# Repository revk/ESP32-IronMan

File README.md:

# ESP32-IronMan

Now at [Codeberg](https://codeberg.org/RevK/ESP32-IronMan)

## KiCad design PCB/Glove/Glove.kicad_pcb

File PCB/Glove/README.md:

# Glove

These files are for use in [KiCad](https://www.kicad.org).

## Trademark

This is an open source project, but bear in mind you cannot sell boards bearing the Andrews & Arnold Ltd name, the A&A logo, the registered trademark AJK logo, or the GS1 allocated EANs assigned to Andrews & Arnold Ltd.

## Images

*Auto generated 2025-01-28T13:22:18*

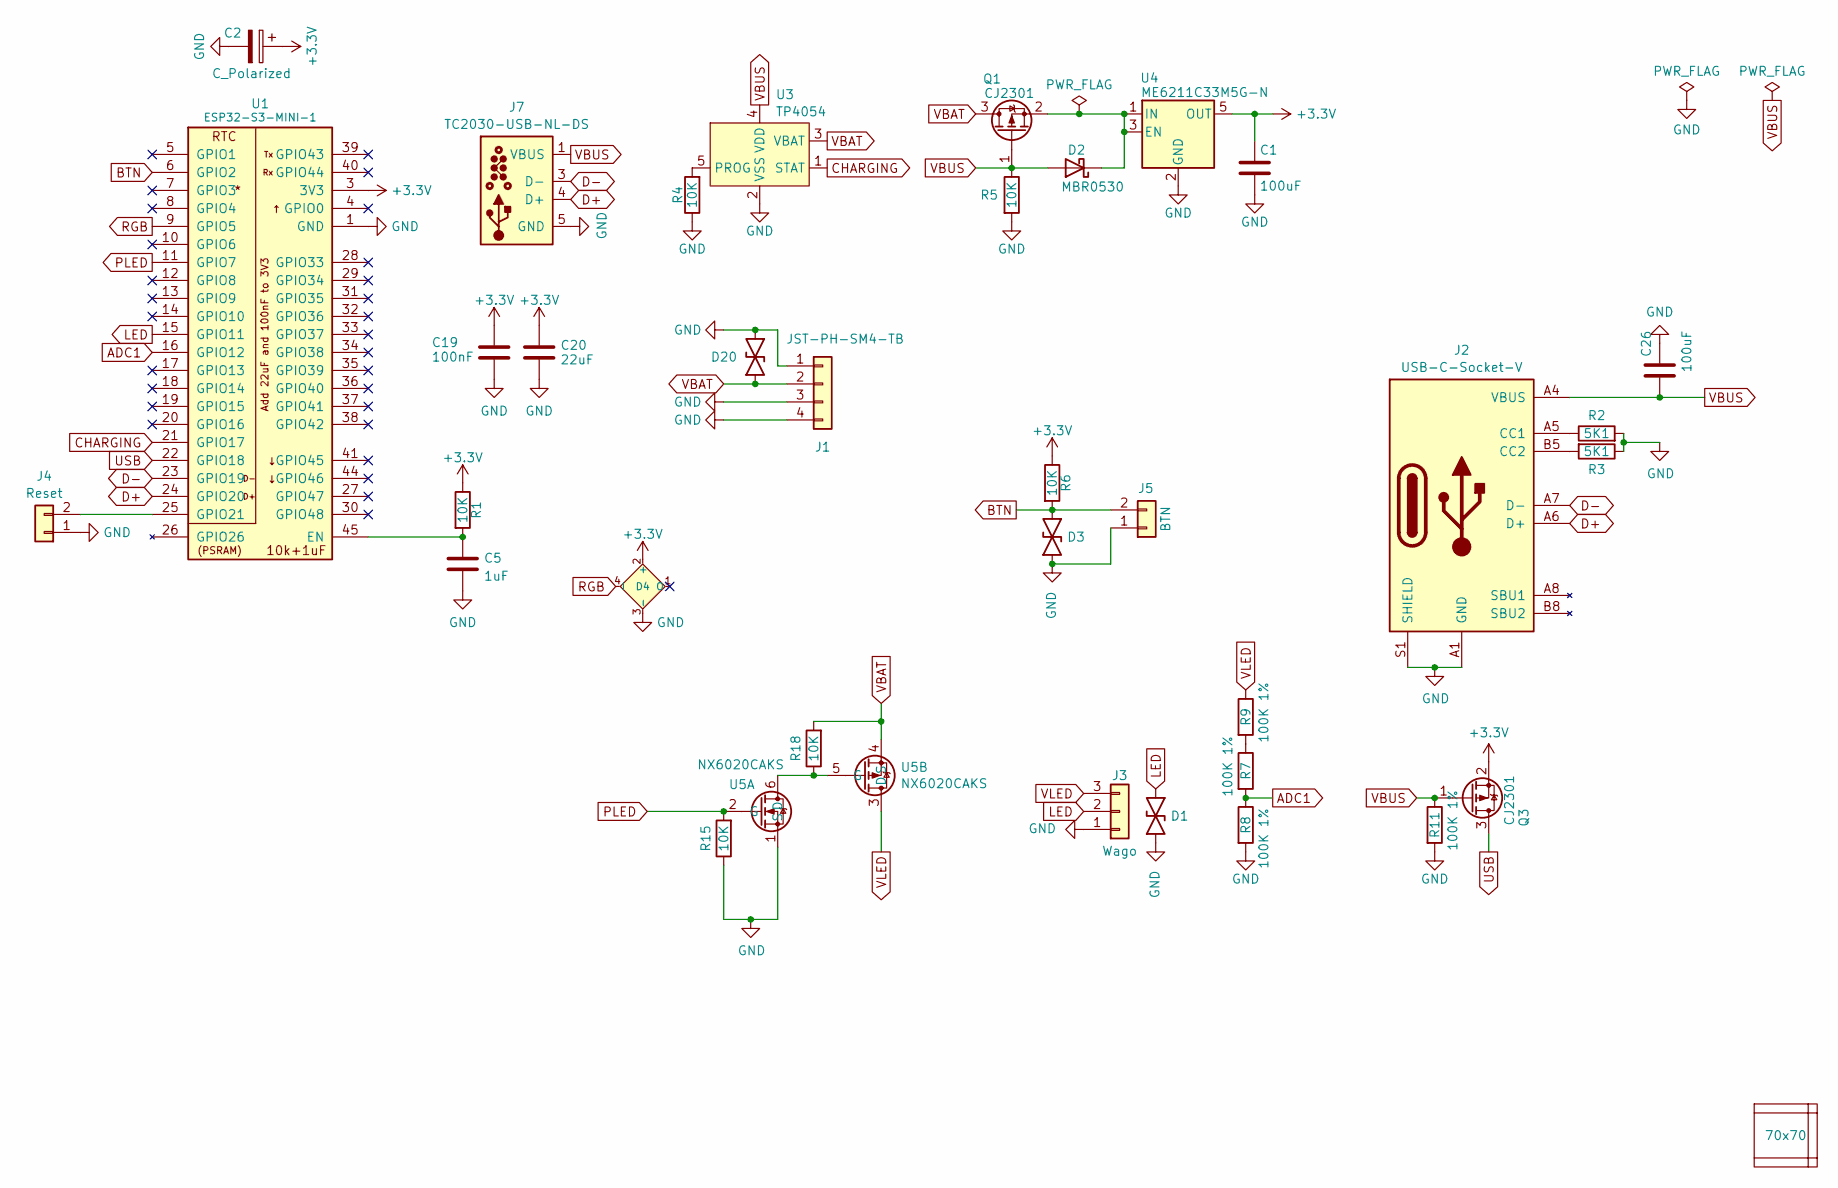
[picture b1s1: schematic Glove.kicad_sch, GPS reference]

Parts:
C1, C26: 100uF; C_0805; MPN C141660
C2: C_Polarized; CP_EIA-7343-31_Kemet-D; MPN C106188
C5: 1uF; C_0402
C19: 100nF; C_0402
C20: 22uF; C_0603
D1, D3, D20: DFN1006-2L; MPN C5137770
D2: MBR0530; D_SOD-123; MPN C5204746
D4: XL-1010RGBC-WS2812B; SMD1010; MPN C5349953
J1: JST-PH-SM4-TB; JST_PH_S2B-PH-SM4-TB_1x02-1MP_P2.00mm_Horizontal; MPN C295747
J2: USB-C-Socket-V; USB-C-Socket-H; MPN C709357
J3: Wago; WAGO-2060-453-998-404; MPN C2765056
J4: Reset; AA-Pad
J5: BTN; WAGO-2060-452-998-404; MPN C2765055
J7: TC2030-USB-NL-DS; Tag-Connect_TC2030-IDC-NL_2x03_P1.27mm_Vertical
PCB1: 70x70; PCB7070
Q1, Q3: CJ2301; SOT-23; MPN C5224170
R1, R4, R5, R6, R15, R18: 10K; R_0402
R2, R3: 5K1; R_0402
R7, R8, R9, R11: 100K 1%; R_0402; MPN C5139597
U1: ESP32-S3-MINI-1; MPN C3013941
U3: TP4054; SOT-23-5; MPN C668215
U4: ME6211C33M5G-N; SOT-23-5; MPN C82942
U5: NX6020CAKS; SOT-363_SC-70-6
V1, V2, V4: VCUT70N

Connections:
+3.3V: C1.1, C2.1, C19.1, C20.1, D4.2 (+), Q3.2 (S), R1.1, R6.1, U1.3 (3V3), U4.5 (OUT)
ADC1: R7.2, R8.1, U1.16 (GPIO12)
BTN: D3.2, J5.2, R6.2, U1.6 (GPIO2)
CHARGING: U1.21 (GPIO17), U3.1 (STAT)
D+: J2.A6 (D+), J2.B6 (D+), J7.4 (D+), U1.24 (GPIO20)
D-: J2.A7 (D-), J2.B7 (D-), J7.2 (NC), J7.3 (D-), J7.6 (NC), U1.23 (GPIO19)
GND: C1.2, C2.2, C5.2, C19.2, C20.2, C26.2, D1.1, D3.1, D4.3 (-), D20.1, J1.1, J1.3, J1.4, J2.A1 (GND), J2.A12 (GND), J2.B1 (GND), J2.B12 (GND), J2.S1 (SHIELD), J3.1, J4.1, J5.1, J7.5 (GND), R2.2, R3.1, R4.1, R5.2, R8.2, R11.2, R15.1, U1.1 (GND), U1.2 (GND), U1.42 (GND), U1.43 (GND), U1.46 (GND), U1.47 (GND), U1.48 (GND), U1.49 (GND), U1.50 (GND), U1.51 (GND), U1.52 (GND), U1.53 (GND), U1.54 (GND), U1.55 (GND), U1.56 (GND), U1.57 (GND), U1.58 (GND), U1.59 (GND), U1.60 (GND), U1.61 (GND), U1.62 (GND), U1.63 (GND), U1.64 (GND), U1.65 (GND), U3.2 (VSS), U4.2 (GND), U5.1 (S)
LED: D1.2, J3.2, U1.15 (GPIO11)
unnamed: D2.1 (K), Q1.2 (S), U4.1 (IN), U4.3 (EN)
unnamed: J2.A5 (CC1), R2.1
unnamed: J2.B5 (CC2), R3.2
unnamed: J4.2, U1.25 (GPIO21)
unnamed: R7.1, R9.2
unnamed: C5.1, R1.2, U1.45 (EN)
unnamed: R4.2, U3.5 (PROG)
unnamed: R18.1, U5.5 (G), U5.6 (D)
PLED: R15.2, U1.11 (GPIO7), U5.2 (G)
RGB: D4.4 (I), U1.9 (GPIO5)
USB: Q3.3 (D), U1.22 (GPIO18)
VBAT: D20.2, J1.2, Q1.3 (D), R18.2, U3.3 (VBAT), U5.4 (S)
VBUS: C26.1, D2.2 (A), J2.A4 (VBUS), J2.A9 (VBUS), J2.B4 (VBUS), J2.B9 (VBUS), J7.1 (VBUS), Q1.1 (G), Q3.1 (G), R5.1, R11.1, U3.4 (VDD)
VLED: J3.3, R9.1, U5.3 (D)

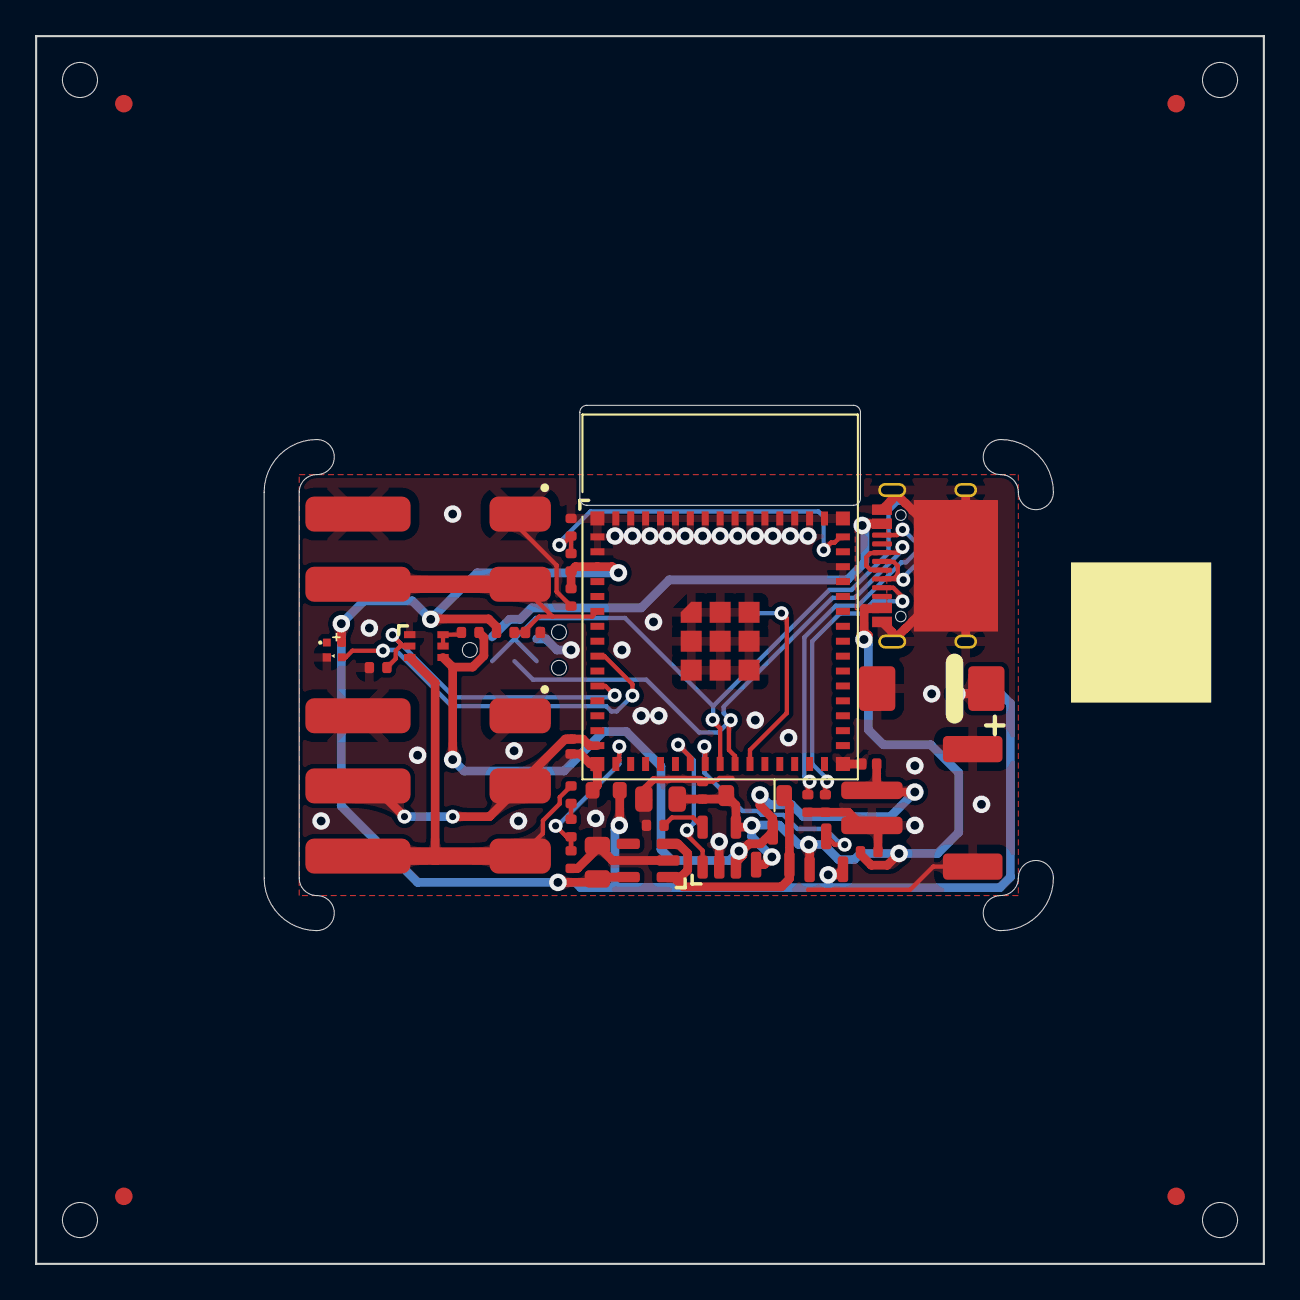
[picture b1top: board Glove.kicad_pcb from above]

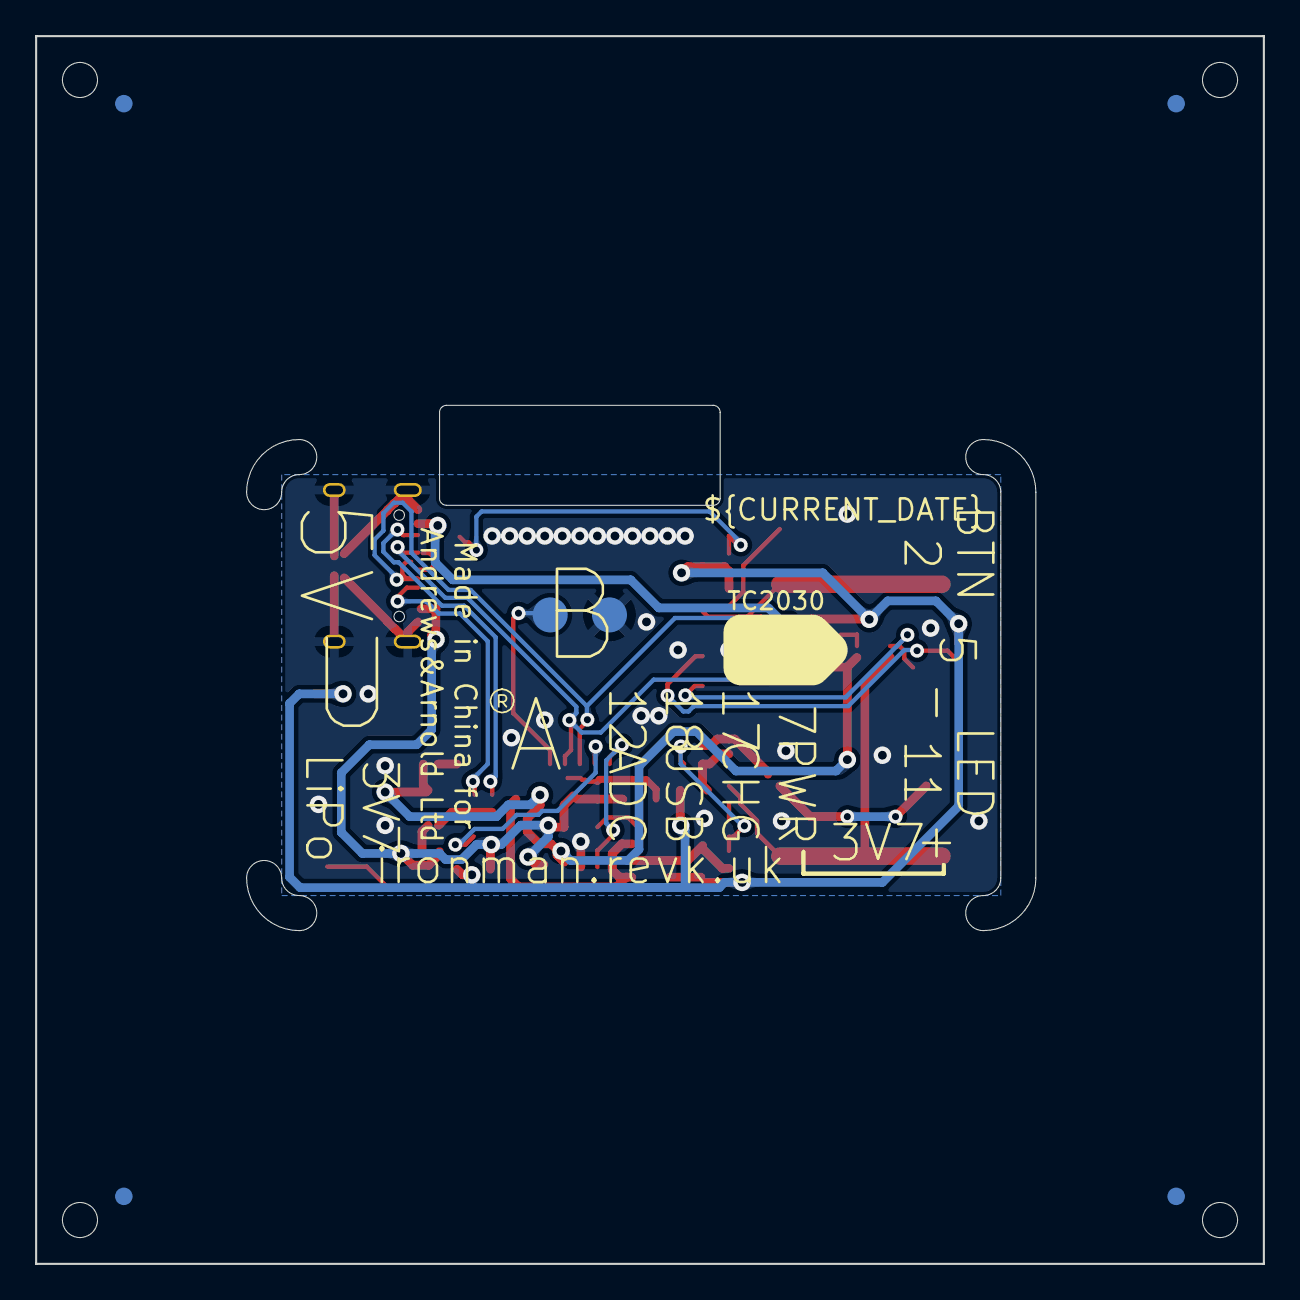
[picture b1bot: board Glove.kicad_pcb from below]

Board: 2 copper layers, 70.0 x 70.0 mm, 39 parts (3 on the bottom side), 22 nets.

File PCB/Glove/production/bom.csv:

Designator,Footprint,Quantity,Value,LCSC Part #
"C1, C26",C_0805,2,100uF,C141660
C19,C_0402,1,100nF,
C2,CP_EIA-7343-31_Kemet-D,1,C_Polarized,C106188
C20,C_0603,1,22uF,
C5,C_0402,1,1uF,
"D1, D20, D3",DFN1006-2L,3,~,C5137770
D2,D_SOD-123,1,MBR0530,C5204746
D4,SMD1010,1,XL-1010RGBC-WS2812B,C5349953
J1,JST_PH_S2B-PH-SM4-TB_1x02-1MP_P2.00mm_Horizontal,1,JST-PH-SM4-TB,C295747
J2,USB-C-Socket-H,1,USB-C-Socket-V,C709357
J3,WAGO-2060-453-998-404,1,Wago,C2765056
J4,AA-Pad,1,Reset,
J5,WAGO-2060-452-998-404,1,BTN,C2765055
"Q1, Q3",SOT-23,2,CJ2301,C5224170
"R1, R15, R18, R4, R5, R6",R_0402,6,10K,
"R11, R7, R8, R9",R_0402,4,100K 1%,C5139597
"R2, R3",R_0402,2,5K1,
U1,ESP32-S3-MINI-1,1,ESP32-S3-MINI-1,C3013941
U3,SOT-23-5,1,TP4054,C668215
U4,SOT-23-5,1,ME6211C33M5G-N,C82942
U5,SOT-363_SC-70-6,1,NX6020CAKS,

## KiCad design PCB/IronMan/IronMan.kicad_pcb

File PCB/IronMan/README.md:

# IronMan

These files are for use in [KiCad](https://www.kicad.org).

## Trademark

This is an open source project, but bear in mind you cannot sell boards bearing the Andrews & Arnold Ltd name, the A&A logo, the registered trademark AJK logo, or the GS1 allocated EANs assigned to Andrews & Arnold Ltd.

## Images

*Auto generated 2025-01-30T09:48:34*

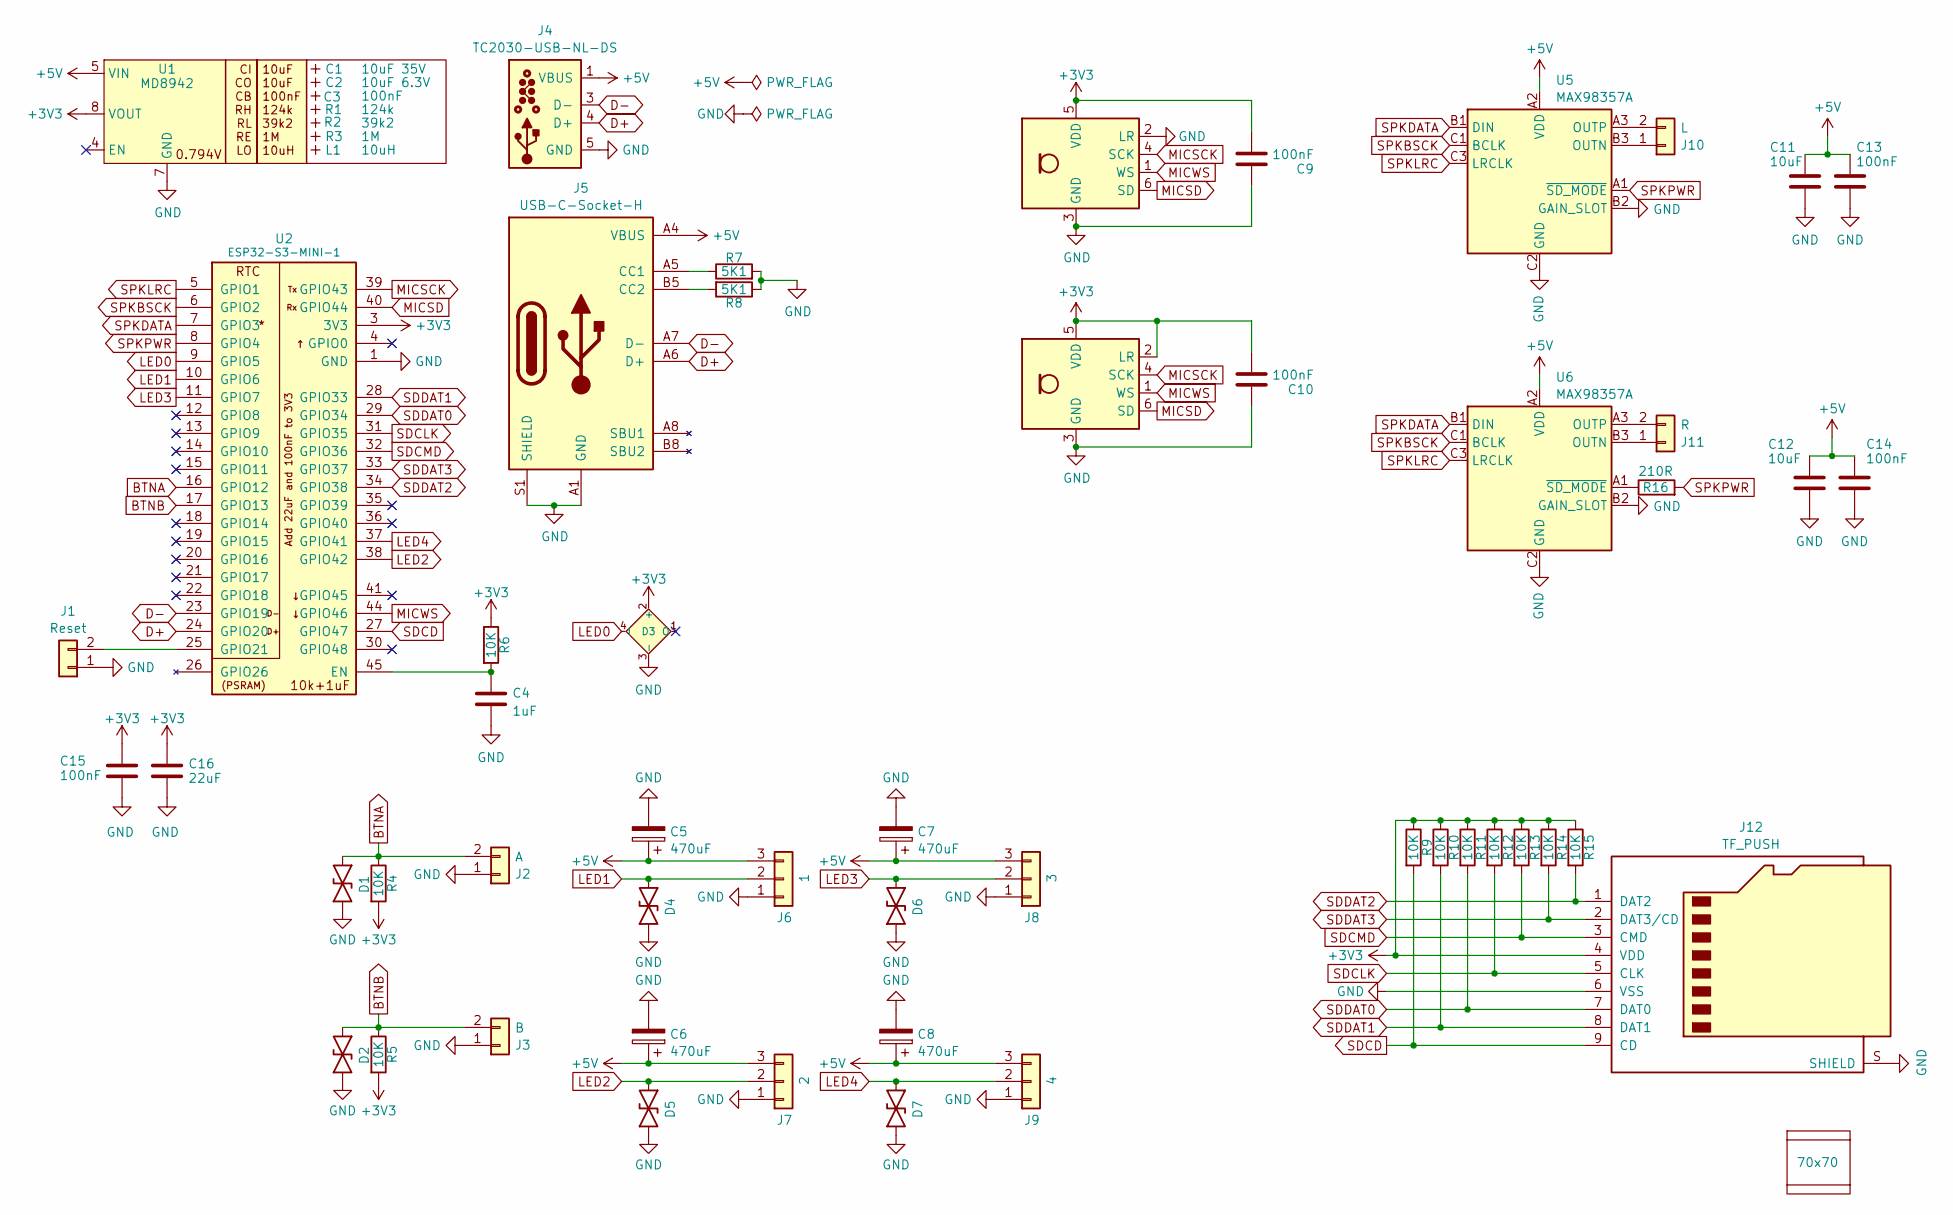
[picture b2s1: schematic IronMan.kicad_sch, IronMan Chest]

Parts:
C1: 10uF 35V; C_0603_; MPN C194427
C2: 10uF 6.3V; C_0603_; MPN C1691
C3: 100nF; C_0603_
C4: 1uF; C_0402
C5, C6, C7, C8: 470uF; CP_EIA-7343-31_Kemet-D; MPN C106188
C9, C10, C13, C14, C15: 100nF; C_0402
C11, C12: 10uF; C_0402; MPN C15525
C16: 22uF; C_0603
D1, D2, D4, D5, D6, D7: DFN1006-2L; MPN C5137770
D3: XL-1010RGBC-WS2812B; SMD1010; MPN C5349953
J1: Reset; AA-Pad
J2: A; WAGO-2060-452-998-404; MPN C2765055
J3: B; WAGO-2060-452-998-404; MPN C2765055
J4: TC2030-USB-NL-DS; Tag-Connect_TC2030-IDC-NL_2x03_P1.27mm_Vertical
J5: USB-C-Socket-H; MPN C709357
J6: 1; WAGO-2060-453-998-404; MPN C2765056
J7: 2; WAGO-2060-453-998-404; MPN C2765056
J8: 3; WAGO-2060-453-998-404; MPN C2765056
J9: 4; WAGO-2060-453-998-404; MPN C2765056
J10: L; WAGO-2060-452-998-404; MPN C2765055
J11: R; WAGO-2060-452-998-404; MPN C2765055
J12: TF_PUSH; MPN C393941
L1: 10uH; L_4x4_
PCB1: 70x70; PCB7070
R1: 124k; R_0402_
R2: 39k2; R_0402_
R3: 1M; R_0402_
R4, R5, R6, R9, R10, R11, R12, R13, R14, R15: 10K; R_0402
R7, R8: 5K1; R_0402
R16: 210R; R_0402; MPN C226891
U1: MD8942; SOT-23-6-MD8942; MPN C2684786
U2: ESP32-S3-MINI-1; MPN C3013941
U3: L; ICS43434_MEMS_Mic; MPN C5656610
U4: R; ICS43434_MEMS_Mic; MPN C5656610
U5, U6: MAX98357A; WLP-1.437mmx1.347mm-0.21mm-ball; MPN C2682619
V2, V3: VCUT70N

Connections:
+3V3: C9.2, C10.2, C15.1, C16.1, D3.2 (+), J12.4 (VDD), R4.2, R5.2, R6.1, R9.1, R10.1, R11.1, R12.1, R13.1, R14.1, R15.1, U1.8 (VOUT), U2.3 (3V3), U3.5 (VDD), U4.2 (LR), U4.5 (VDD)
+5V: C5.1, C6.1, C7.1, C8.1, C11.1, C12.1, C13.1, C14.1, J4.1 (VBUS), J5.A4 (VBUS), J5.A9 (VBUS), J5.B4 (VBUS), J5.B9 (VBUS), J6.3, J7.3, J8.3, J9.3, U1.5 (VIN), U5.A2 (VDD), U6.A2 (VDD)
BTNA: D1.1, J2.2, R4.1, U2.16 (GPIO12)
BTNB: D2.1, J3.2, R5.1, U2.17 (GPIO13)
D+: J4.4 (D+), J5.A6 (D+), J5.B6 (D+), U2.24 (GPIO20)
D-: J4.2 (NC), J4.3 (D-), J4.6 (NC), J5.A7 (D-), J5.B7 (D-), U2.23 (GPIO19)
GND: C4.2, C5.2, C6.2, C7.2, C8.2, C9.1, C10.1, C11.2, C12.2, C13.2, C14.2, C15.2, C16.2, D1.2, D2.2, D3.3 (-), D4.2, D5.2, D6.2, D7.2, J1.1, J2.1, J3.1, J4.5 (GND), J5.A1 (GND), J5.A12 (GND), J5.B1 (GND), J5.B12 (GND), J5.S1 (SHIELD), J6.1, J7.1, J8.1, J9.1, J12.6 (VSS), J12.S (SHIELD), R7.2, R8.1, U1.2 (GND), U1.7 (GND), U2.1 (GND), U2.2 (GND), U2.42 (GND), U2.43 (GND), U2.46 (GND), U2.47 (GND), U2.48 (GND), U2.49 (GND), U2.50 (GND), U2.51 (GND), U2.52 (GND), U2.53 (GND), U2.54 (GND), U2.55 (GND), U2.56 (GND), U2.57 (GND), U2.58 (GND), U2.59 (GND), U2.60 (GND), U2.61 (GND), U2.62 (GND), U2.63 (GND), U2.64 (GND), U2.65 (GND), U3.2 (LR), U3.3 (GND), U4.3 (GND), U5.B2 (GAIN_SLOT), U5.C2 (GND), U6.B2 (GAIN_SLOT), U6.C2 (GND)
LED0: D3.4 (I), U2.9 (GPIO5)
LED1: D4.1, J6.2, U2.10 (GPIO6)
LED2: D5.1, J7.2, U2.38 (GPIO42)
LED3: D6.1, J8.2, U2.11 (GPIO7)
LED4: D7.1, J9.2, U2.37 (GPIO41)
MICSCK: U2.39 (GPIO43), U3.4 (SCK), U4.4 (SCK)
MICSD: U2.40 (GPIO44), U3.6 (SD), U4.6 (SD)
MICWS: U2.44 (GPIO46), U3.1 (WS), U4.1 (WS)
unnamed: J1.2, U2.25 (GPIO21)
unnamed: J5.A5 (CC1), R7.1
unnamed: J5.B5 (CC2), R8.2
unnamed: J10.1, U5.B3 (OUTN)
unnamed: J10.2, U5.A3 (OUTP)
unnamed: J11.1, U6.B3 (OUTN)
unnamed: J11.2, U6.A3 (OUTP)
unnamed: C4.1, R6.2, U2.45 (EN)
unnamed: R16.1, U6.A1 (~SD_MODE)
SDCD: J12.9 (CD), R9.2, U2.27 (GPIO47)
SDCLK: J12.5 (CLK), R12.2, U2.31 (GPIO35)
SDCMD: J12.3 (CMD), R13.2, U2.32 (GPIO36)
SDDAT0: J12.7 (DAT0), R11.2, U2.29 (GPIO34)
SDDAT1: J12.8 (DAT1), R10.2, U2.28 (GPIO33)
SDDAT2: J12.1 (DAT2), R15.2, U2.34 (GPIO38)
SDDAT3: J12.2 (DAT3/CD), R14.2, U2.33 (GPIO37)
SPKBSCK: U2.6 (GPIO2), U5.C1 (BCLK), U6.C1 (BCLK)
SPKDATA: U2.7 (GPIO3), U5.B1 (DIN), U6.B1 (DIN)
SPKLRC: U2.5 (GPIO1), U5.C3 (LRCLK), U6.C3 (LRCLK)
SPKPWR: R16.2, U2.8 (GPIO4), U5.A1 (~SD_MODE)

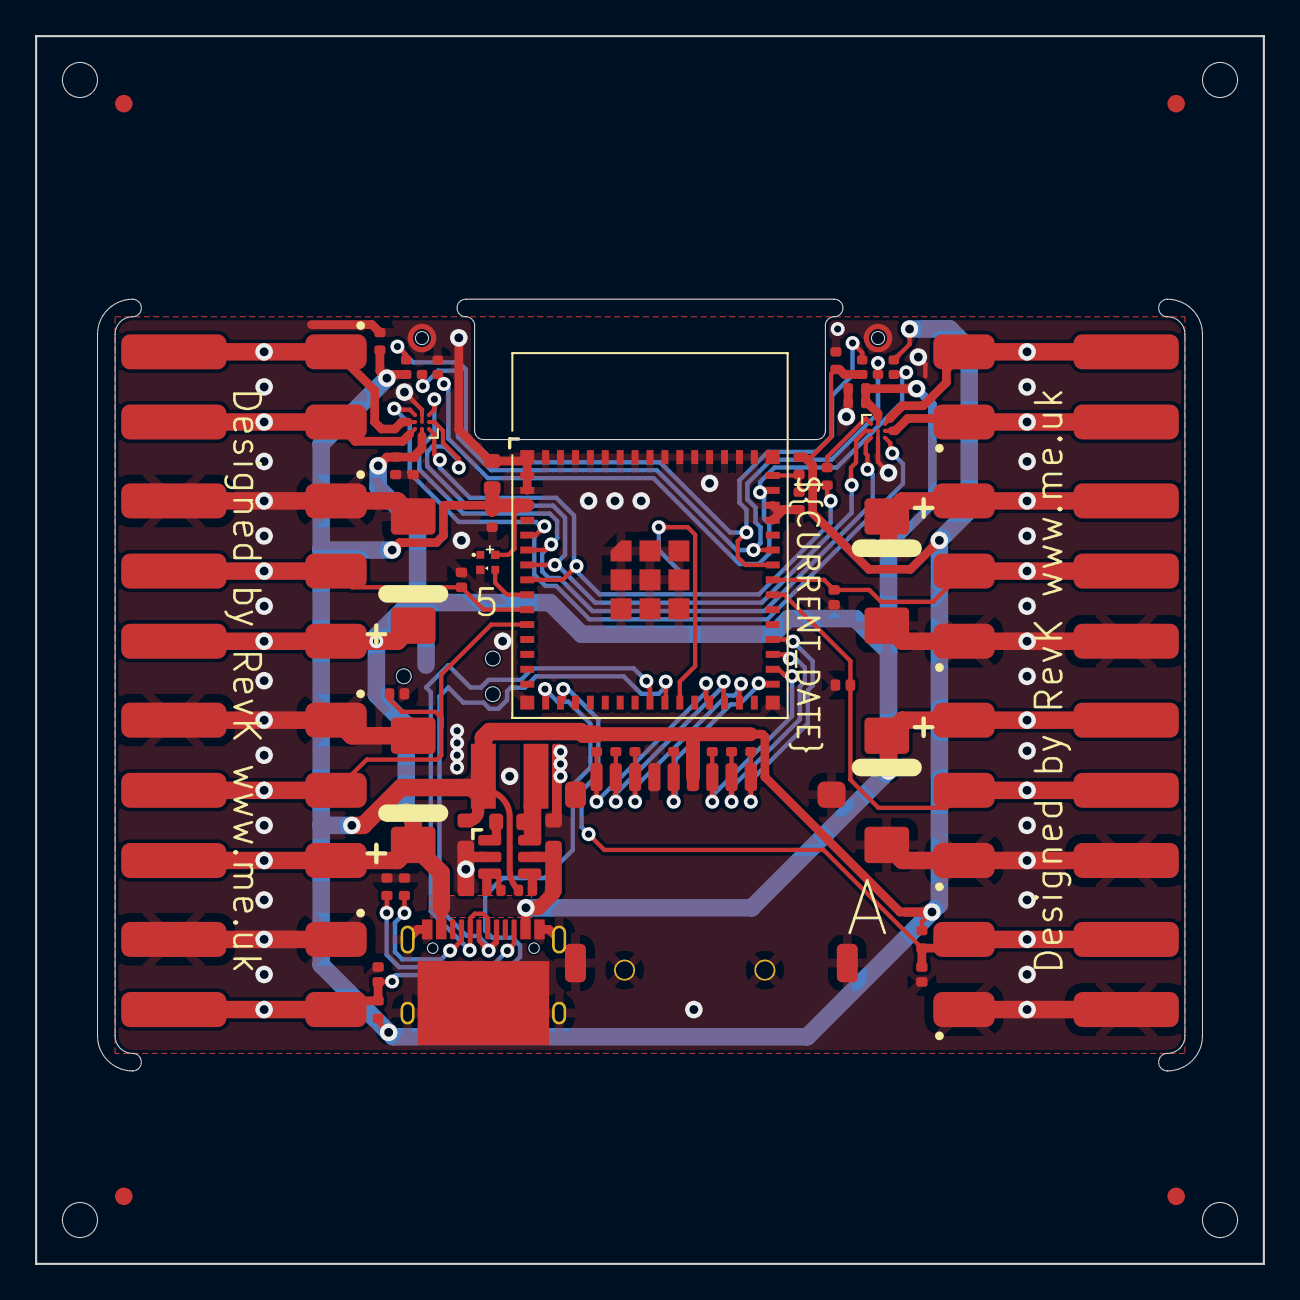
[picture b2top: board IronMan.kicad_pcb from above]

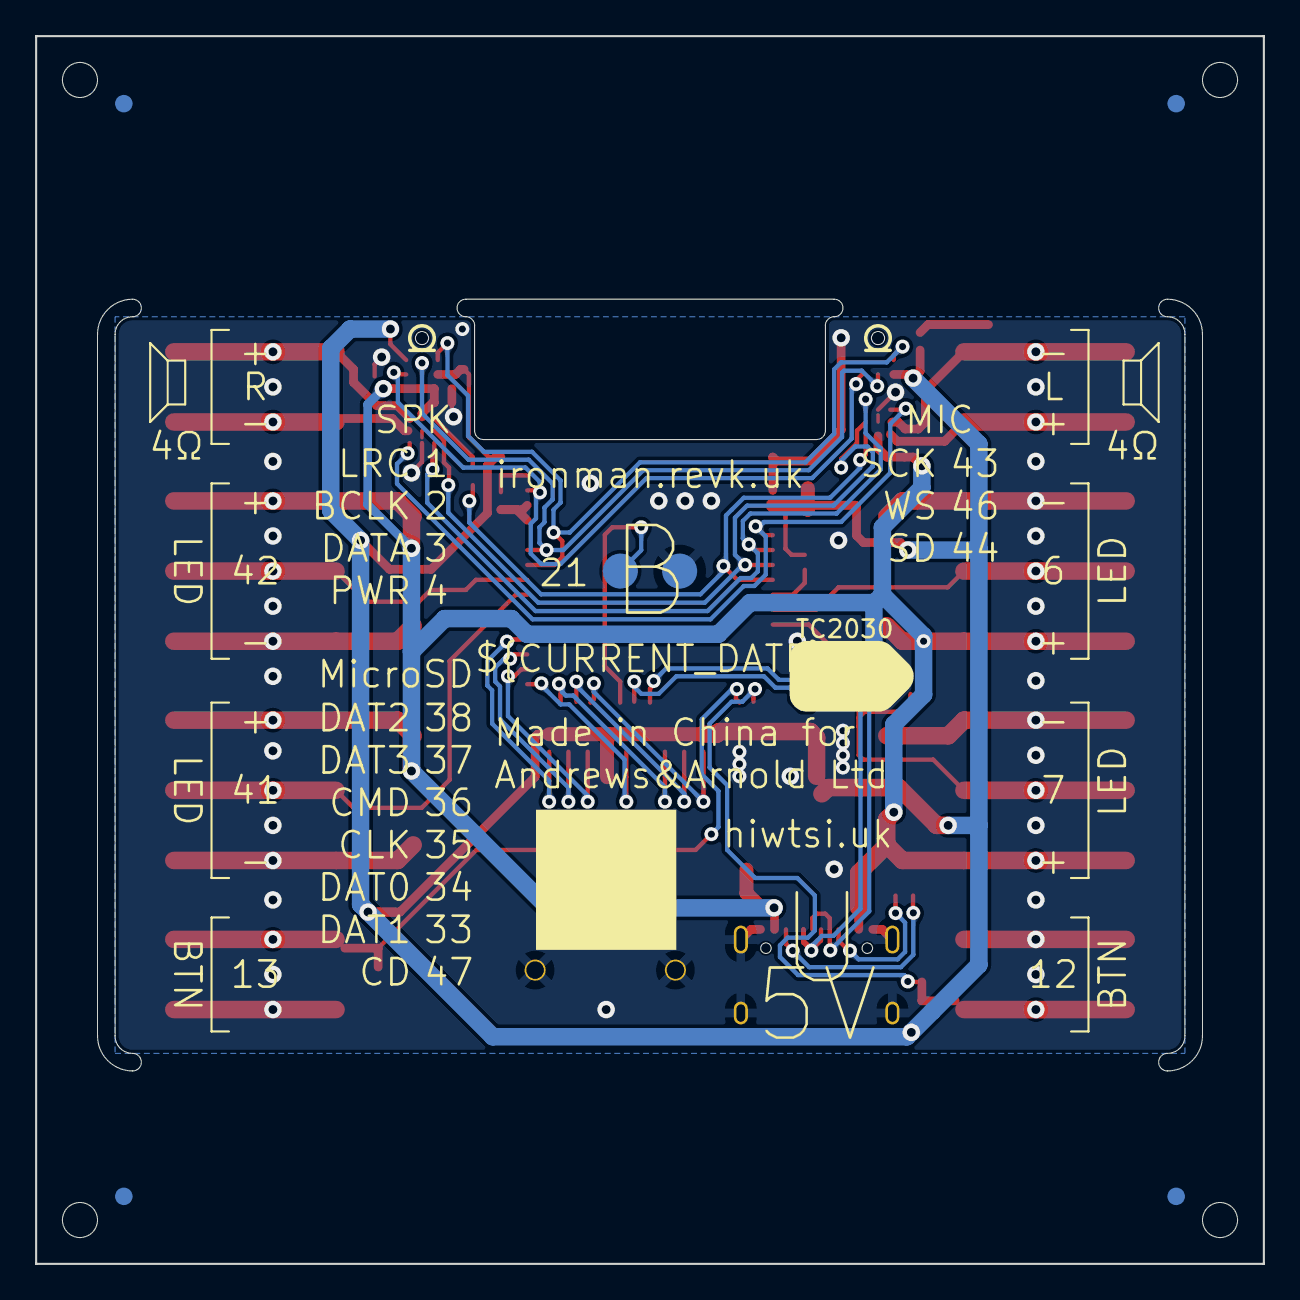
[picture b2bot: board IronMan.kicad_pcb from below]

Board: 2 copper layers, 70.0 x 70.0 mm, 61 parts (2 on the bottom side), 35 nets.

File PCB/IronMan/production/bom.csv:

Designator,Footprint,Quantity,Value,LCSC Part #
C1,C_0603_,1,10uF 35V,C194427
"C10, C13, C14, C15, C9",C_0402,5,100nF,
"C11, C12",C_0402,2,10uF,C15525
C16,C_0603,1,22uF,
C2,C_0603_,1,10uF 6.3V,C1691
C3,C_0603_,1,100nF,
C4,C_0402,1,1uF,
"C5, C6, C7, C8",CP_EIA-7343-31_Kemet-D,4,470uF,C106188
"D1, D2, D4, D5, D6, D7",DFN1006-2L,6,~,C5137770
D3,SMD1010,1,XL-1010RGBC-WS2812B,C5349953
J10,WAGO-2060-452-998-404,1,L,C2765055
J11,WAGO-2060-452-998-404,1,R,C2765055
J12,TF_PUSH,1,TF_PUSH,C393941
J2,WAGO-2060-452-998-404,1,A,C2765055
J3,WAGO-2060-452-998-404,1,B,C2765055
J5,USB-C-Socket-H,1,USB-C-Socket-H,C709357
J6,WAGO-2060-453-998-404,1,1,C2765056
J7,WAGO-2060-453-998-404,1,2,C2765056
J8,WAGO-2060-453-998-404,1,3,C2765056
J9,WAGO-2060-453-998-404,1,4,C2765056
L1,L_4x4_,1,10uH,
R1,R_0402_,1,124k,
"R10, R11, R12, R13, R14, R15, R4, R5, R6, R9",R_0402,10,10K,
R16,R_0402,1,210R,C226891
R2,R_0402_,1,39k2,
R3,R_0402_,1,1M,
"R7, R8",R_0402,2,5K1,
U1,SOT-23-6-MD8942,1,MD8942,C2684786
U2,ESP32-S3-MINI-1,1,ESP32-S3-MINI-1,C3013941
U3,ICS43434_MEMS_Mic,1,L,C5656610
U4,ICS43434_MEMS_Mic,1,R,C5656610
"U5, U6",WLP-1.437mmx1.347mm-0.21mm-ball,2,MAX98357A,C2682619

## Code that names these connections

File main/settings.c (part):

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#define	BUTTONS	2
 {.type=REVK_SETTINGS_UNSIGNED,.isenum=1,.name="ironman",.comment="What part",.len=7,.def="1",.ptr=&ironman,.size=sizeof(uint8_t),.enums="Suit,Helmet,Left Glove,Right Glove"	},
 {.type=REVK_SETTINGS_UNSIGNED,.gpio=1,.name="button",.comment="Activation buttons",.len=6,.def="-12,-13",.ptr=&button,.size=sizeof(revk_gpio_t),.fix=1,.set=1,.flags="- ~↓↕⇕",.array=BUTTONS},
 {.type=REVK_SETTINGS_UNSIGNED,.gpio=1,.name="stripgpio",.comment="GPIOs for LED string",.group=1,.len=9,.dot=5,.def="6,7,41",.ptr=&stripgpio,.size=sizeof(revk_gpio_t),.fix=1,.set=1,.flags="- ~↓↕⇕",.array=STRIPS,.old="rgb"		},
 {.type=REVK_SETTINGS_UNSIGNED,.name="stripcount",.comment="How many LEDs in string",.group=1,.len=10,.dot=5,.def="12",.ptr=&stripcount,.size=sizeof(uint16_t),.array=STRIPS,.old="leds"	},
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 {.type=REVK_SETTINGS_UNSIGNED,.gpio=1,.name="sddat2",.comment="MicroSD DAT2",.group=2,.len=6,.dot=2,.def="38",.ptr=&sddat2,.size=sizeof(revk_gpio_t),.fix=1,.set=1,.flags="- ~↓↕⇕"},
 {.type=REVK_SETTINGS_UNSIGNED,.gpio=1,.name="sddat3",.comment="MicroSD DAT3",.group=2,.len=6,.dot=2,.def="37",.ptr=&sddat3,.size=sizeof(revk_gpio_t),.fix=1,.set=1,.flags="- ~↓↕⇕",.old="sdss"	},
 {.type=REVK_SETTINGS_UNSIGNED,.gpio=1,.name="sdcmd",.comment="MicroSD CMD",.group=2,.len=5,.dot=2,.def="36",.ptr=&sdcmd,.size=sizeof(revk_gpio_t),.fix=1,.set=1,.flags="- ~↓↕⇕",.old="sdmosi"	},
 {.type=REVK_SETTINGS_UNSIGNED,.gpio=1,.name="sdclk",.comment="MicroSD CLK",.group=2,.len=5,.dot=2,.def="35",.ptr=&sdclk,.size=sizeof(revk_gpio_t),.fix=1,.set=1,.flags="- ~↓↕⇕",.old="sdsck"	},
 {.type=REVK_SETTINGS_UNSIGNED,.gpio=1,.name="sddat0",.comment="MicroSD DAT0",.group=2,.len=6,.dot=2,.def="34",.ptr=&sddat0,.size=sizeof(revk_gpio_t),.fix=1,.set=1,.flags="- ~↓↕⇕",.old="sdmiso"	},
 {.type=REVK_SETTINGS_UNSIGNED,.gpio=1,.name="sddat1",.comment="MicroSD DAT1",.group=2,.len=6,.dot=2,.def="33",.ptr=&sddat1,.size=sizeof(revk_gpio_t),.fix=1,.set=1,.flags="- ~↓↕⇕"},
 {.type=REVK_SETTINGS_UNSIGNED,.gpio=1,.name="sdcd",.comment="MicroSD CD",.group=2,.len=4,.dot=2,.def="-47",.ptr=&sdcd,.size=sizeof(revk_gpio_t),.fix=1,.set=1,.flags="- ~↓↕⇕"},
 {.type=REVK_SETTINGS_UNSIGNED,.gpio=1,.name="micdata",.comment="Microphone Data / SD",.group=3,.len=7,.dot=3,.def="44",.ptr=&micdata,.size=sizeof(revk_gpio_t),.fix=1,.set=1,.flags="- ~↓↕⇕"},
 {.type=REVK_SETTINGS_UNSIGNED,.gpio=1,.name="micclock",.comment="Microphone Clock / SCK",.group=3,.len=8,.dot=3,.def="43",.ptr=&micclock,.size=sizeof(revk_gpio_t),.fix=1,.set=1,.flags="- ~↓↕⇕"},
 {.type=REVK_SETTINGS_UNSIGNED,.gpio=1,.name="micws",.comment="Microphone WS (not set for PDM)",.group=3,.len=5,.dot=3,.def="46",.ptr=&micws,.size=sizeof(revk_gpio_t),.fix=1,.set=1,.flags="- ~↓↕⇕"},
 {.type=REVK_SETTINGS_UNSIGNED,.gpio=1,.name="spkpwr",.comment="Speaker power on",.group=4,.len=6,.dot=3,.def="4",.ptr=&spkpwr,.size=sizeof(revk_gpio_t),.fix=1,.set=1,.flags="- ~↓↕⇕"},
 {.type=REVK_SETTINGS_UNSIGNED,.gpio=1,.name="spklrc",.comment="Speaker LR clock",.group=4,.len=6,.dot=3,.def="1",.ptr=&spklrc,.size=sizeof(revk_gpio_t),.fix=1,.set=1,.flags="- ~↓↕⇕"},
 {.type=REVK_SETTINGS_UNSIGNED,.gpio=1,.name="spkbclk",.comment="Speaker Bit clock",.group=4,.len=7,.dot=3,.def="2",.ptr=&spkbclk,.size=sizeof(revk_gpio_t),.fix=1,.set=1,.flags="- ~↓↕⇕"},
 {.type=REVK_SETTINGS_UNSIGNED,.gpio=1,.name="spkdata",.comment="Speaker Data",.group=4,.len=7,.dot=3,.def="3",.ptr=&spkdata,.size=sizeof(revk_gpio_t),.fix=1,.set=1,.flags="- ~↓↕⇕"},
 {.type=REVK_SETTINGS_UNSIGNED,.gpio=1,.name="usb",.comment="USB connected",.len=3,.ptr=&usb,.size=sizeof(revk_gpio_t),.fix=1,.set=1,.flags="- ~↓↕⇕"},
 {.type=REVK_SETTINGS_UNSIGNED,.gpio=1,.name="chg",.comment="Charge indicator",.len=3,.ptr=&chg,.size=sizeof(revk_gpio_t),.fix=1,.set=1,.flags="- ~↓↕⇕"},
 {.type=REVK_SETTINGS_UNSIGNED,.name="ledeye1",.comment="LED number for eye 1",.group=5,.len=7,.dot=3,.ptr=&ledeye1,.size=sizeof(uint8_t),.live=1},
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revk_gpio_t stripgpio[STRIPS]={0};
uint16_t stripcount[STRIPS]={0};
uint8_t striptype[STRIPS]={0};
revk_gpio_t sddat2={0};
revk_gpio_t sddat3={0};
revk_gpio_t sdcmd={0};
revk_gpio_t sdclk={0};
revk_gpio_t sddat0={0};
revk_gpio_t sddat1={0};
revk_gpio_t sdcd={0};
revk_gpio_t micdata={0};
revk_gpio_t micclock={0};
revk_gpio_t micws={0};
revk_gpio_t spkpwr={0};
revk_gpio_t spklrc={0};
revk_gpio_t spkbclk={0};
revk_gpio_t spkdata={0};
revk_gpio_t usb={0};
revk_gpio_t chg={0};
uint8_t ledeye1=0;
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
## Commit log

2024-04-21 Library update
2024-04-21 Not building yet
2024-04-21 FFS why no linky?
2024-04-21 Really
2024-04-21 Tidy
2024-04-21 LED strip init
2024-04-21 Proof of concept
2024-04-22 Working
2024-08-14 Error check
2024-08-14 checkpoint
2024-08-14 Release
2024-08-14 Library update and cleaner working
2024-08-25 Push lag (1s)
2024-08-25 Beta
2024-08-25 Arc and pulse
2024-08-25 More LEDs
2024-08-28 Quick startup
2024-08-31 more eyes and cylon
2024-08-31 Shutdown and startup tweaks
2024-08-31 Double click cylon, single click helmet, cleaner
2024-09-01 Colour config
2024-09-01 Config fixed colours
2024-09-01 White pulse, and cleaner init
2024-09-01 edit angle live
2024-09-01 Clean up live settings
2025-01-09 Started
2025-01-10 Started Chest board
2025-01-10 Start on design
2025-01-10 Bigger caps
2025-01-10 Tracked
2025-01-11 Tweak tracks
2025-01-12 New render
2025-01-12 Render
2025-01-12 Try again
2025-01-12 Artwork
2025-01-12 Images
2025-01-12 Cropped
2025-01-13 Rename
2025-01-13 New images
2025-01-13 Check build
2025-01-13 Tweak
2025-01-13 New settings
2025-01-13 Moved settings
2025-01-13 moved beta
2025-01-16 Ready to track
2025-01-16 Ready to order
2025-01-17 Process rails
2025-01-21 Tweak - 5V MAX
2025-01-21 No point
2025-01-22 Ready to re-order
2025-01-22 New more general settings
2025-01-22 Started on SD/SPK logic
2025-01-22 Start on speaker
2025-01-22 Start on SD/WAV
2025-01-22 Dependency
2025-01-22 Basic LED
2025-01-22 Pos files
2025-01-23 PCB Update
2025-01-24 LEDs
2025-01-24 new LED colour logic
2025-01-24 WAV play
2025-01-24 More checks
2025-01-25 Generic button logic
2025-01-25 Upgrade
2025-01-25 Helmet cleanop
2025-01-25 Slow start helmet
2025-01-25 Suit type
2025-01-25 Better
2025-01-25 Restart message
2025-01-26 Power down logic
2025-01-26 Better power on/off logic
2025-01-26 Blink during upgrade
2025-01-26 Blink on s/w u/g
2025-01-26 Glove effect
2025-01-26 Demo BLE server code
2025-01-26 Cutting down GATT logic
2025-01-27 Started work on BLE
2025-01-27 BLE client/server connection working
2025-01-27 Reconnect clean
2025-01-27 Write handler cleanup
2025-01-27 Remote sounds working
2025-01-27 CYLON
2025-01-27 manual
2025-01-27 Glitch
2025-01-27 less debug
2025-01-28 Glitch on 2
2025-01-28 Image eupdates
2025-01-30 Defaults
2025-01-30 blink
2025-01-31 PWM shutdown
2025-01-31 press on start logic
2025-02-02 Tried periodic wake, did not work
2025-02-10 Tweaks
2025-02-10 Charger logic
2025-02-10 Charge logic
2025-02-10 Glitch shutdown
2025-02-10 Helmet start closed
2025-02-10 Charge
2025-03-14 Added ADC and PWR
2026-02-13 submodule
2026-02-15 Codeberg
